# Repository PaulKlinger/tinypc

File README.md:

# TinyPC / ThinkTiny

This repository contains the code, 3d models, and PCB files for my tiny gaming pc and tiny thinkpad. Both projects runs with same code.

| | |
|---------| ---------|
|  |  |

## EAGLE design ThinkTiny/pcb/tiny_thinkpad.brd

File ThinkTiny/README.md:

# ThinkTiny — A miniature laptop

Components:
- [ATtiny1614 microcontroller](https://octopart.com/attiny1614-ssfr-microchip-82181131)
- [128x64 OLED screen with SSD1306 driver](https://www.aliexpress.com/item/Free-Shipping-White-Blue-Whiteand-Blue-color-0-96-inch-128X64-OLED-Display-Module-For-arduino/32713614136.html)
- [5 way switch](https://www.aliexpress.com/item/32807613480.html)
- [WS2812B LED](https://www.aliexpress.com/item/100pcs-DC5V-WS2812B-4Pins-5050-SMD-with-Built-in-WS2811-IC-Individually-Addressable-Digital-RGB-LED/32542036874.html)
- [2mm PMMA optic fiber](https://www.aliexpress.com/item/5mX-Transparent-side-glow-plastic-PMMA-fiber-optic-cable-solid-core-optic-cable-diameter-2mm-3mm/32807597828.html)
- [power switch](https://www.aliexpress.com/item/32967873133.html)
- [TP5400 charge controller/boost converter](https://www.aliexpress.com/item/32869425291.html)
- [10uH CD54 inductor](https://www.aliexpress.com/item/32956022325.html)
- [Li-ion battery](https://www.aliexpress.com/item/32954488360.html)
- [SS24 diode](https://www.aliexpress.com/item/32904408053.html)
- [10K/6.8K/1K 0805 resistor](https://www.aliexpress.com/item/32880368264.html)
- [5x 47uf 1206 capacitors](https://www.aliexpress.com/item/32373728015.html)
- [2xred 1xgreen 0805 led](https://www.aliexpress.com/item/32816842323.html)
- [Some 30 AWG wire wire](https://www.aliexpress.com/item/30-AWG-Wrapping-Wire-0-25mm-Tin-Plated-Copper-8-Colored-Wire-Wrap-Insulation-Test-Cable/32907507087.html)

I cut off the top of the OLED PCB with flush cutters to make it fit into the case. That's where the pin header sits, so I needed to tap into the connections somewhere else on the PCB. I've marked the points in [this image](black_oled_pin_connection_points.jpg), but be careful, there might be versions of this display with different layout. I also added a capacitor after the voltage regulator on the display board (the three pin component). This gets rid of flickering when there's a lot of white on the screen.

To fit the knob on the 5-way switch the stem needs to be cut off just after the thick section at the top. The knob fits pretty well, but to make sure it doesn't come off I used a drop of superglue to fix it in place. Make sure to turn it upside down while glueing, otherwise the glue runs down into the switch and it stops working...

There's a small piece of fiberoptic in the hole in the display back cover, which transmits and diffuses the light from the red LED. That 0805 LED is directly soldered to an 0805 6.8k resistor and connected back to the main PCB.

The plastic pieces are all printed in PLA with a 0.25mm nozzle and 0.1mm layer height on my [Prusa MK3s](https://shop.prusa3d.com/en/3d-printers/180-original-prusa-i3-mk3-kit.html#). No supports are needed, all the pieces have a flat side to put down on the bed. STL files and the Fusion 360 source file (in case anyone wants to edit them) are in the "3d models" directory. The pcb cover ("pcb cover.stl") is printed with a color change: black filament at the bottom (the top when assembled) and then transparent filament to create the diffuser for the "think" logo and the charging indicator LEDs. I raised the first layer height slightly when printing the pcb cover, so that the keys and "think" font wouldn't get squished together.

The hole on the top right of the pcb cover is used to reprogram the MCU without disassembling everything. I use a small jig with three spring loaded pogo pins ([bought here](https://www.aliexpress.com/item/50pcs-set-New-P75-B1-Dia-1-02mm-100g-Cusp-Spear-Spring-Loaded-Test-Probes-Pogo/32767984398.html)) to connect to three pads (for power, ground, and UPDI data) on the PCB underneath (you need to put some solder in the three holes to make a surface for the pins to push against). The holes are the standard pin header ones, 0.1 inch apart, so you can just solder the pogo pins into three adjacent holes of another protoboard to make a jig. Here's [a picture](https://raw.githubusercontent.com/PaulKlinger/ndice/master/programming_jig.jpg) of the programming jig with a PICkit 4 connected (the PICkit doesn't provide power, so that comes from the usb).

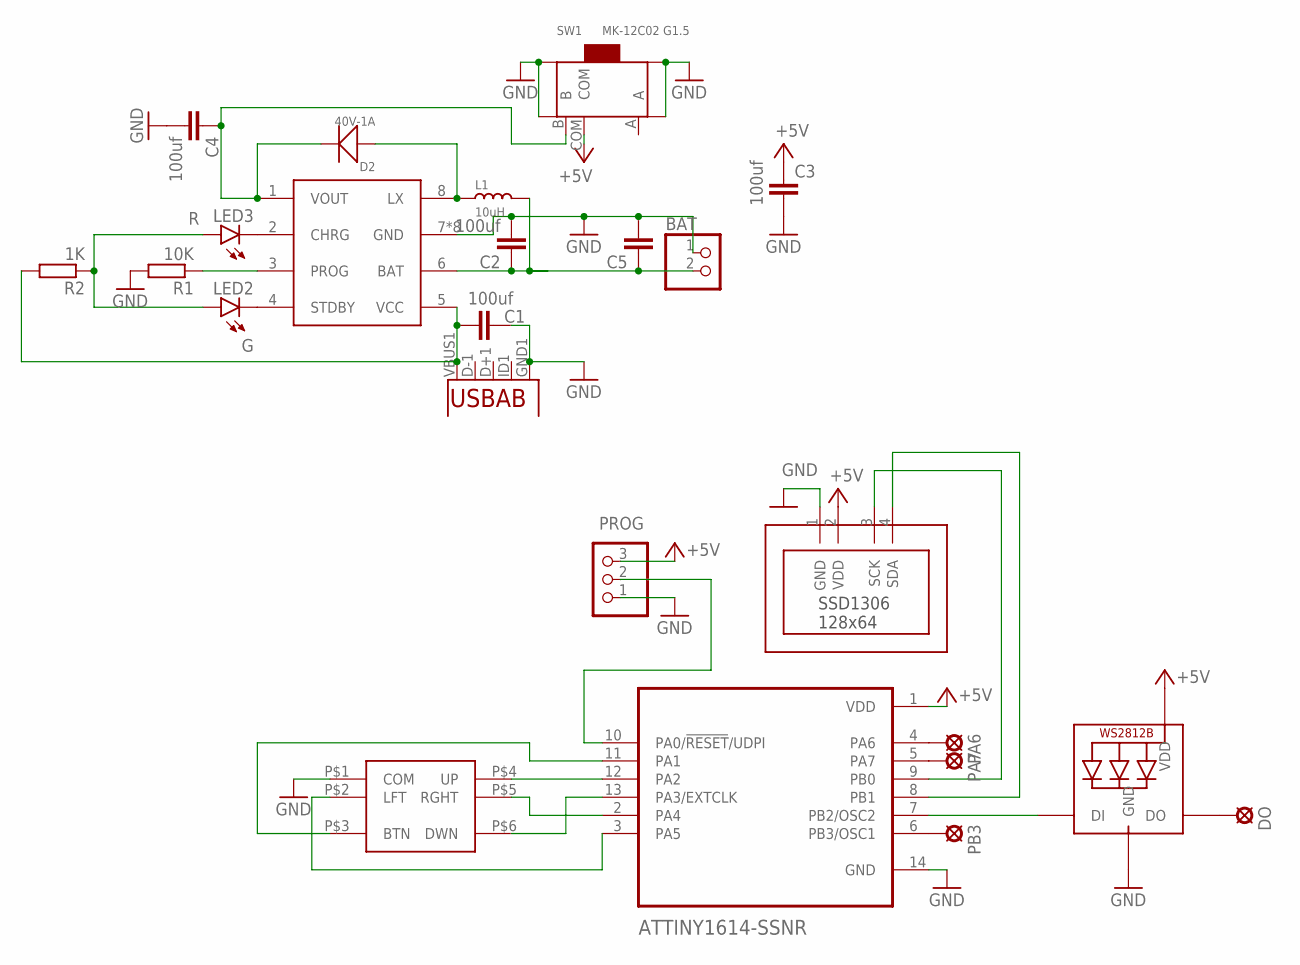
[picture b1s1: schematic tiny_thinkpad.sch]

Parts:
AT1614: ATTINY1614-SSNR; SOIC127P600X175-14N
BAT: PINHD-1X2; 1X02
C1, C2, C3, C4, C5: 100uf; C1206
D2: 40V-1A; DO-214AC
DISP: SSD1306_128X64_OLEDPINHEAD; 1X04-CLEANBIG
DO: LSP10
L1: 10uH; L5040S
LED1: WS2812B5050; WS2812B
LED2: G; SML0805
LED3: R; SML0805
PA6, PA7: LSP10
PB3: LSP10
PROG: PINHD-1X3; 1X03
R1: 10K; R0805
R2: 1K; R0805
SW1: MK-12C02 G1.5; SW7-SMD-L6.7X2.7X3.2MM
U2: USB-THROUGH; USB-MICRO-THROUGH
U$3: TP5400; SOP-8
U$4: 5WAY_SMD_SWITCH; SUNROM_5WAY_SMD_SWITCH

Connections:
+5V: AT1614.1 (VDD), C3.1, DISP.2 (VDD), LED1.1-VDD (VDD), PROG.3, SW1.COM
GND: AT1614.14 (GND), BAT.1, C1.1, C2.2, C3.2, C4.2, C5.2, DISP.1 (GND), LED1.3-GND (GND), PROG.1, R1.2, SW1.SS1, SW1.SS2, SW1.SS3, SW1.SS4, U2.GND1 (GND), U$3.7 (GND), U$3.BOTTOM (GND), U$3.P$1 (GND), U$3.P$2 (GND), U$3.P$3 (GND), U$3.P$4 (GND), U$3.P$5 (GND), U$3.P$6 (GND), U$4.P$1 (COM)
unnamed: C4.1, D2.2 (-), SW1.B, U$3.1 (VOUT)
unnamed: AT1614.10 (PA0/!RESET!/UDPI), PROG.2
unnamed: AT1614.11 (PA1), U$4.P$3 (BTN)
unnamed: AT1614.13 (PA3/EXTCLK), U$4.P$6 (DWN)
unnamed: AT1614.2 (PA4), U$4.P$5 (RGHT)
unnamed: AT1614.12 (PA2), U$4.P$4 (UP)
unnamed: AT1614.3 (PA5), U$4.P$2 (LFT)
unnamed: AT1614.7 (PB2/OSC2), LED1.4-DIN (DI)
unnamed: R1.1, U$3.3 (PROG)
unnamed: BAT.2, C2.1, C5.1, L1.2, U$3.6 (BAT)
unnamed: D2.1 (+), L1.1, U$3.8 (LX)
unnamed: C1.2, R2.2, U2.VBUS1 (VBUS), U$3.5 (VCC)
unnamed: LED2.C, U$3.4 (STDBY)
unnamed: LED3.C, U$3.2 (CHRG)
unnamed: LED2.A, LED3.A, R2.1
unnamed: AT1614.4 (PA6), PA6.MP
unnamed: AT1614.5 (PA7), PA7.MP
unnamed: AT1614.6 (PB3/OSC1), PB3.MP
unnamed: DO.MP, LED1.2-DOUT (DO)
SCK: AT1614.9 (PB0), DISP.3 (SCK)
SDA: AT1614.8 (PB1), DISP.4 (SDA)

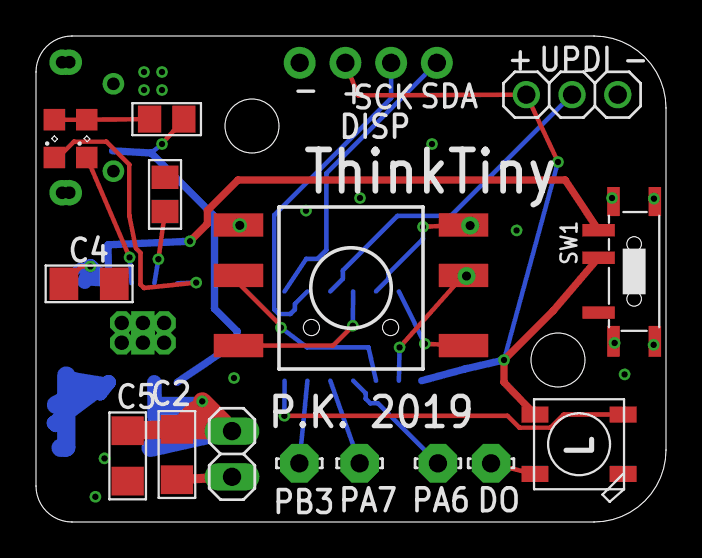
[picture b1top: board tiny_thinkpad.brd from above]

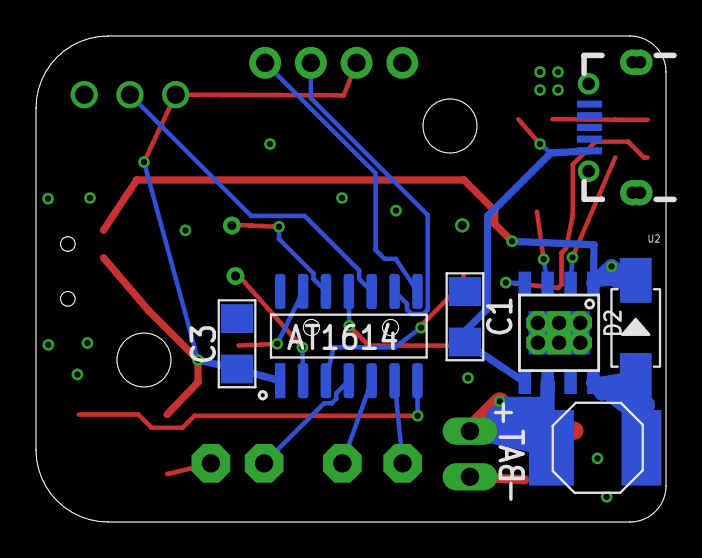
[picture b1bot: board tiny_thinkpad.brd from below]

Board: 2 copper layers, 35.0 x 27.0 mm, 24 parts (7 on the bottom side), 23 nets.

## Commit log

2019-02-08 inital commit, stl files
2019-02-08 added fusion 360 design file
2019-02-08 added code for Attiny1614 MCU
2019-02-08 added readme
2019-02-08 corrected video link
2019-02-08 added MCC config
2019-02-09 use lcd_goto_xpix_y for lcd_gotoxy
2019-02-09 updated video link, added list of components
2019-02-09 added programming info
2019-02-09 added note about window printing
2019-02-09 added threaded inserts to parts list
2019-02-10 added fiber coupling .stl file
2019-02-10 use interrupts to catch fast joystick movements
2019-02-10 initialize joystick direction on reset
2019-02-10 collected snake variables into struct
2019-02-10 code reorganization
    moved snake game to separate file (preperation for multiple applications)
2019-02-10 added basic menu
2019-02-10 some basic debouncing (not great...)
2019-02-10 better debouncing
2019-02-10 added game of life with random init
2019-02-10 set optimization to O2
2019-02-10 prevent instant exit from gol
2019-02-11 made local functions static
    prevents namespace conflicts between applications
2019-02-12 started work on breakout
    currently bouncing ball and static blocks, next todo is collision with blocks
2019-02-12 made modulo function inlineable
    Not inlining modulo seriously reduced update rate in gol (to 2/s or so)
2019-02-12 added breakout to menu, reorganization
2019-02-12 added todo comment to gol
2019-02-12 truncate display_block region
2019-02-12 breakout progress
    ball destroys blocks, paddle still todo
2019-02-13 correctly truncate display_block region
2019-02-13 breakout progress
    added movable paddle, todo: paddle collision
2019-02-13 working breakout game
2019-02-13 factored out game over screen to utilities
2019-02-13 parameter tweaks
2019-02-13 draw and display paddle separately
    otherwise flickering occurs when ball hits paddle
2019-02-13 final(ish) breakout, multiple stages
2019-02-13 added rgb to gol and breakout
2019-02-13 updated readme: now plays more than snake :)
2019-02-14 added fillTriangle function to lcd.c
2019-02-14 added mandelbrot viewer
    very unoptimized atm
2019-02-14 use fixed instead of floating point math
2019-02-14 binary and mcc updates
2019-02-15 set I2C baudrate to 800kHz
    I'm sure I did this before??
2019-02-15 got rid of all the floats...
    ... at the cost of pretty ugly workaround in normalize_ball_v
2019-02-15 only calc new tiles on movement
2019-02-15 bugfix for move_left, made point_in_set_correct
2019-02-15 added rotate function, changed breakout to use it
    This replaces the one ugly workaround in normalize_ball_v with several slightly less ugly ones. Yay!...?
2019-02-15 improved fillTriangle function
2019-02-15 added u8vec and accvec add function
2019-02-15 started work on lunar lander game
    Mostly working, just conditions for successful landing and scoring stuff missing. But progmem is at 99% so, need to work on that first.
2019-02-15 save a tiny bit of memory in mcc code
2019-02-15 saved some space in lcd
    got rid of doublesized and special chars
2019-02-16 added common strings, randrange, srand in main
2019-02-16 complete lander game, "procedural" terrain, multiple stages
2019-02-16 reordered menu entries
2019-02-16 added rgb to lander, mandelbrot
    for lander: points
    for mandelbrot: number of calculated 8x8 px blocks
2019-02-16 menu tweaks
2019-02-16 updated binaries
2019-02-16 highlight landing pad, tweaked collision
2019-02-17 changed video link to new video
2019-02-17 updated video link image
2019-03-21 added schematic
2019-07-12 made compatible with black pcb version of OLED
2019-07-15 added led dim factor (for laptop)
2019-07-17 changed title string for tiny laptop & added config
2019-07-18 added ThinkTiny, reorganized
2019-07-18 lander: don't abort stage when pressing button
2019-07-19 moved bit matrix functions to utilities
2019-07-19 simplified button handling
2019-07-21 fixed a stupid bug in randrange...
2019-07-21 added tetris game, removed breakout (until bigger attiny)
2019-07-22 show next piece
2019-07-27 prevent moving pieces out of play area while they are entering
2019-07-27 set led color from points for tetris
2019-07-27 updated 3d models
2019-07-28 added link to thinktiny video
2019-07-28 resized link images
2019-07-28 Revert "resized link images"
    This reverts commit add9673c88dccb06101f5a7f9a66392219c47fd8.
2019-07-28 fixed markdown
2019-07-28 added parts list for thinktiny
2019-07-28 added gerbers and schematic pdf
2019-07-28 deleted empty file
2019-07-28 added some comments
2019-07-28 some assembly tips added
2019-07-28 added some more detail to readme
2019-07-28 some more assembly tips
2019-07-29 added some info about 3d prints
2019-07-30 removed redundant line
2019-07-31 more 3d print details
2019-07-31 renamed randrange to randint to be more consistent with python (upper bound is included in interval)
2019-08-01 save some bytes in tetris by optimizing long function for size
2019-08-01 added minesweeper, still need to add win condition (and probably save some bytes somewhere)
2019-08-01 save some bytes in lcd.c (mostly removing bounds checking)
2019-08-01 saved a few more bytes
2019-08-01 finished minesweeper (win condition, remaining mines,...)
2019-08-01 remove autogenerated makefiles from repository
2019-08-01 prevent flagging a revealed cell, save some bytes
2019-08-02 removed binaries from repo (available in github releases)
2019-08-02 Don't draw incorrect flags at game end
2019-08-16 changed default led color to red for thinktiny
2019-08-16 increased starting and max speed
2019-08-16 adjusted max speed
2019-11-17 added delay before display init, removed unused file
    On one of the ThinkTinys the display would only work after turning it
    on-off-on. Adding a small delay before makes it work consistently,
    probably because the voltage has time to stabilise.
    Removed unused/empty autogenerated slpcontrol file to get the
    required space. There's some more potential to save space there.
